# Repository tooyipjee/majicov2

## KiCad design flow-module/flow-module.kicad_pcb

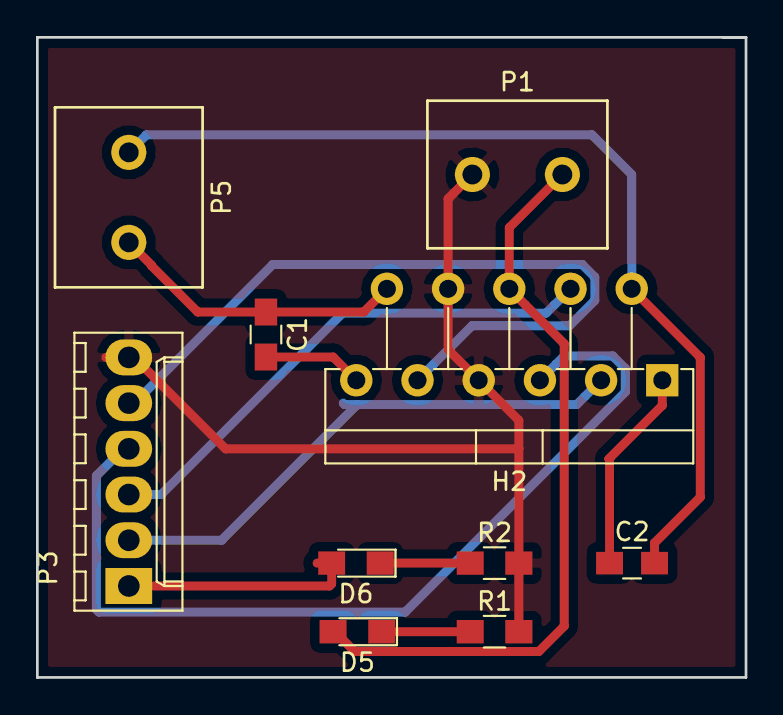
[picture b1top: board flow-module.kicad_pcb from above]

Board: 2 copper layers, 39.4 x 35.6 mm, 10 parts (0 on the bottom side), 13 nets.

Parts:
C1, C2: C; C_0805_HandSoldering
D5, D6: LED; LED_0805_HandSoldering
H2: LMD18201T; TO-220-11
P1, P5: TERM_01X02; TE_TERM
P3: MOLEX_01X06; Molex_KK-6410-06_06x2.54mm_Straight
R1: 680; R_0805_HandSoldering
R2: 330; R_0805_HandSoldering

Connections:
Brake: H2.4, P3.3
Dir: H2.3, P3.2
Earth: H2.7, H2.8, P1.2, P3.6, R1.2, R2.2
Flag: H2.9, P3.5
unnamed: C1.2, H2.11
unnamed: C2.1, H2.1
unnamed: D5.1, R1.1
unnamed: D6.1, R2.1
Output1: C2.2, H2.2, P5.2
Output2: C1.1, H2.10, P5.1
PWM: H2.5, P3.4
VAA: D6.2, P3.1
VCC: D5.2, H2.6, P1.1

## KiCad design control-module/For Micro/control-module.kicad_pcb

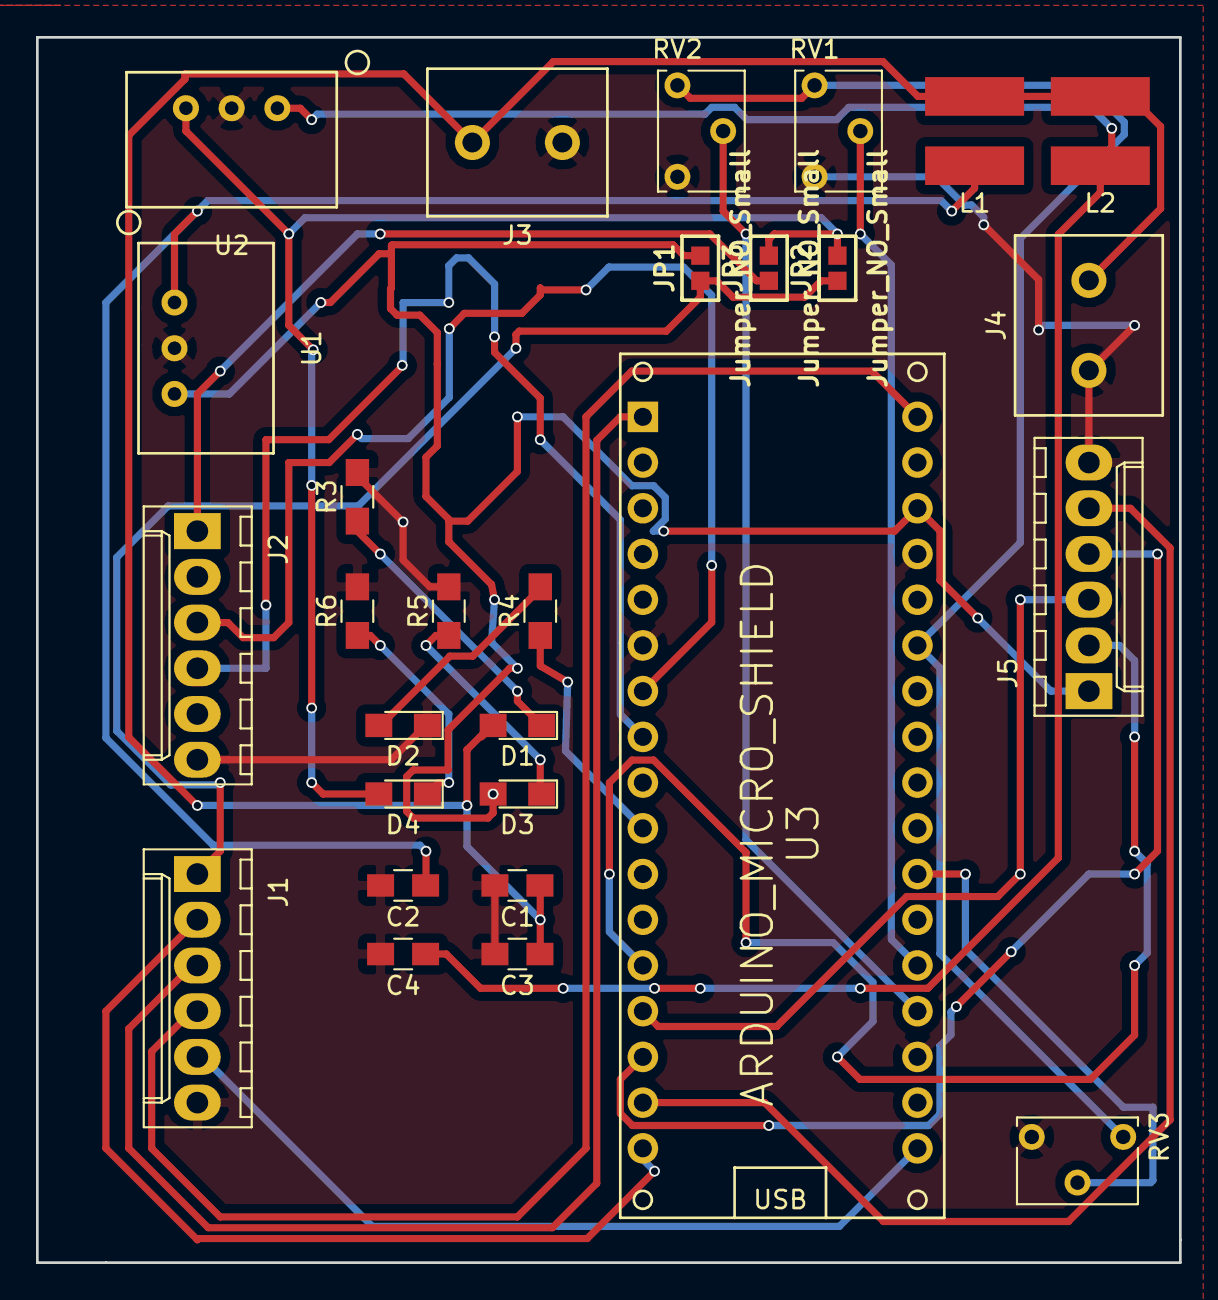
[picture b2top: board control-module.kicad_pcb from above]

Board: 2 copper layers, 63.5 x 68.1 mm, 28 parts (0 on the bottom side), 27 nets.

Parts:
C1, C2, C3, C4: 10uF; C_0805_HandSoldering
D1, D2, D3, D4: LED; LED_0805_HandSoldering
J1: For Expansion; Molex_KK-6410-06_06x2.54mm_Straight
J2: For Light Sensor; Molex_KK-6410-06_06x2.54mm_Straight
J3: From Solar Panel; TE_TERM
J4: To Flow Module (F); TE_TERM
J5: For Flow Module b; Molex_KK-6410-06_06x2.54mm_Straight
JP1, JP2, JP3: Jumper_NO_Small; SMD-solder-bridge
L1, L2: 6.8uH; WURTH_INDUCTOR
R3: 680; R_0805_HandSoldering
R4, R5, R6: 470; R_0805_HandSoldering
RV1, RV3: Trimmer Upper; Potentiometer_Trimmer_Vishay_T73XX_Vertical
RV2: Trimmer Lower; Potentiometer_Trimmer_Vishay_T73XX_Vertical
U1, U2: TR_SERIES; TR_Series
U3: ARDUINO_MICRO_SHIELD

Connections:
5V: RV1.1, RV2.1, RV3.1, U3.5V
12V: C1.1, C3.1, D1.2, J3.1, J4.1, L1.1, L2.1
A0: RV2.2, U3.A0
A1: RV1.2, U3.A1
A3: RV3.2, U3.A3
DEBUG1: J1.2, U3.12
DEBUG2: J1.5, U3.13
GND: C1.2, C2.2, C3.2, C4.2, D2.1, J1.6, J2.6, J3.2, J4.2, J5.6, R3.2, R5.2, R6.2, RV1.3, RV2.3, RV3.3, U1.GND, U2.GND, U3.AREF, U3.GND
INPUT2: J5.2, U3.8
INPUT3: J5.3, U3.9
INPUT4: J5.4, U3.10
INPUT5: J5.5, U3.11
MISO: J1.4, U3.SCK
MOSI: J1.3, U3.MO
unnamed: C2.1, L1.2, U1.VI
unnamed: C4.1, L2.2, U2.VI
unnamed: D1.1, R3.1
unnamed: D2.2, R4.2
unnamed: D3.1, R5.1
unnamed: D4.1, R6.1
SCLA: J2.4, U3.3
SDAA: J2.3, U3.2
TEST: R4.1, U3.5
VCC+3V: D4.2, JP2.2, JP3.2, U2.VO
VCC+5V: D3.2, J5.1, JP1.2, U1.VO, U3.VI
VCC+EXP: J1.1, JP1.1, JP2.1
VCC+LS: J2.1, JP3.1

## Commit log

2018-08-16 Old files
2018-08-18 PCB Design update
2018-08-18 Added ground planes and remove unnecessary tracks
2018-08-19 Removed light module
2018-09-14 Added Drill, Gerber and PDFs
2018-09-14 Update to PCB
2018-09-14 Removed old Gerber, Drill files
2018-09-14 Gerber, Drill, PDFs for Flow Module
2018-09-14 Gerber files for Control Mod
2018-09-23 Made flow board even smaller
2018-09-23 Saved changes
2018-09-23 saved changes.
2018-09-24 Replaced with proper drill file
2018-09-24 Added Drill File
